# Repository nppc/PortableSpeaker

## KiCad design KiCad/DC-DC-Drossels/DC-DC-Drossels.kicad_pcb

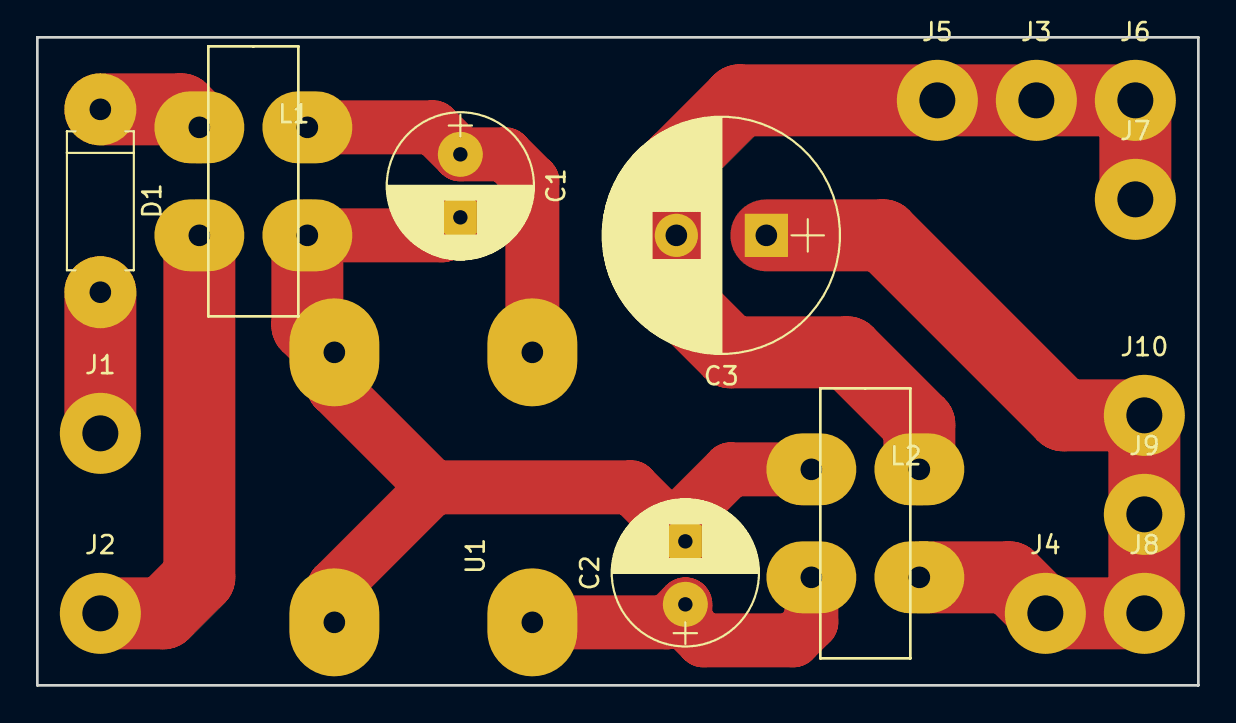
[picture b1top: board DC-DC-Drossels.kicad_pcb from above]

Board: 2 copper layers, 64.5 x 36.0 mm, 17 parts (0 on the bottom side), 8 nets.

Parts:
C1, C2: CP; CP_Radial_D8.0mm_P3.50mm
C3: CP; CP_Radial_D13.0mm_P5.00mm
D1: D_Schottky; D_DO-15_P10.16mm_Horizontal
J1, J2, J3, J4, J5, J6, J7, J8, J9, J10: Conn_01x01; SolderWirePad_single_2mmDrill
L1, L2: L_Core_Ferrite_Coupled; L_CommonMode_Wuerth_WE-CMB-XS
U1: MP1584ENBB; DIP-4_W7.62mm

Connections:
GND: C1.2, C2.2, L1.4, L2.1, U1.2, U1.3
unnamed: C1.1, L1.2, U1.1
unnamed: C2.1, L2.3, U1.4
unnamed: C3.1, J4.1, J8.1, J9.1, J10.1, L2.4
unnamed: C3.2, J3.1, J5.1, J6.1, J7.1, L2.2
unnamed: D1.1, L1.1
unnamed: D1.2, J1.1
unnamed: J2.1, L1.3

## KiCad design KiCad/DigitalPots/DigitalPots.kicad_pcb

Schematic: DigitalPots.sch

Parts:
C1: 2uf; C_0603
C2: 10n; C_0603
C3: 10uf; C_0603
C4: 100n; C_0603
J1: i2c; Conn_1x03_2.54mm
J2: 3; Conn_1x03_2.54mm
J3: 1; Conn_1x03_2.54mm
J4: 2; Conn_1x03_2.54mm
J5: 0; Conn_1x03_2.54mm
J6: Conn_01x02; Conn_1x02_2.54mm
J7: PWR; Conn_1x02_2.54mm
JP1: A0; SolderJumper-3_P1.3mm_Open_Pad1.0x1.5mm_NumberLabels
JP2: A1; SolderJumper-3_P1.3mm_Open_Pad1.0x1.5mm_NumberLabels
JP3: WP; SolderJumper-3_P1.3mm_Open_Pad1.0x1.5mm_NumberLabels
R1: 10k; R_0603
U1: LP2985-5.0; SOT-23-5
U2: IC20; TSSOP-20_4.4x6.5mm_Pitch0.65mm

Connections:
+9V: C1.1, J7.2, U1.1 (VIN), U1.3 (ON/~OFF~)
/A0: JP1.2, U2.4
/A1: JP2.2, U2.16
/RST: J6.1, R1.2, U2.15
/SCL: J1.3, U2.5
/SDA: J1.2, U2.6
/WP: J6.2, JP3.2, U2.14
GND: C1.2, C2.2, C3.2, C4.2, J1.1, J7.1, JP1.3, JP2.3, JP3.3, U1.2 (GND), U2.7
unnamed: C2.1, U1.4 (BP)
unnamed: J2.1, U2.3
unnamed: J2.2, U2.2
unnamed: J2.3, U2.1
unnamed: J3.1, U2.10
unnamed: J3.2, U2.9
unnamed: J3.3, U2.8
unnamed: J4.1, U2.20
unnamed: J4.2, U2.19
unnamed: J4.3, U2.18
unnamed: J5.1, U2.13
unnamed: J5.2, U2.12
unnamed: J5.3, U2.11
VCC: C3.1, C4.1, JP1.1, JP2.1, JP3.1, R1.1, U1.5 (VOUT), U2.17

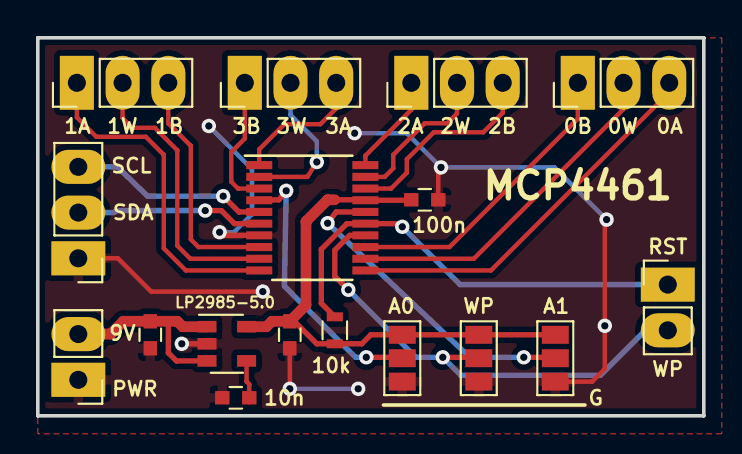
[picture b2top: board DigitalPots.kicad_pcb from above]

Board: 2 copper layers, 37.0 x 21.0 mm, 17 parts (0 on the bottom side), 22 nets.

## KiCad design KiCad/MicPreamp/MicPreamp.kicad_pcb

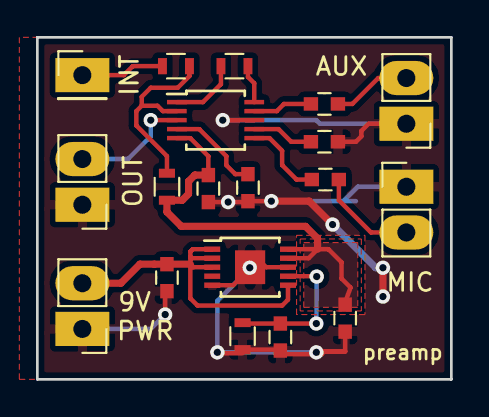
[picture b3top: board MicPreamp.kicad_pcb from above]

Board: 2 copper layers, 23.0 x 19.0 mm, 19 parts (0 on the bottom side), 15 nets.

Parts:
C1, C7: 100n; C_0603
C2, C8: 10uf; C_0603
C3: 0.47uf; C_0603
C4, C5, C6: 1uf; C_0603
J1: PWR; Conn_1x02_2.54mm
J2: INT; Conn_1x01_2.54mm
J3: OUT; Conn_1x02_2.54mm
J4: AUX; Conn_1x02_2.54mm
J5: MIC; Conn_1x02_2.54mm
R1: 100; R_0603
R2: 100K; R_0603
R3: 11K; R_0603
R4: 50K; R_0603
U1: MAX4062; TSSOP-10_3x3mm_Pitch0.5mm
U2: LT3042; MSOP-10-1EP_3x3mm_Pitch0.5mm

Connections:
+9V: C2.1, J1.2, U2.1, U2.2, U2.3, U2.6
/AUX_IN: C4.2, U1.9
/BIAS: C1.2, U1.4
/G1: R3.1, U1.10
/G2: R3.2, U1.1
/IN+: C6.2, U1.6
/IN-: C5.2, U1.7
/INT: R1.1, R2.1, U1.2
/OUT: J3.2, U1.3
GND: C1.1, C2.2, C3.2, C5.1, C7.2, C8.2, J1.1, J3.1, J4.1, J5.1, R4.1, U1.8, U2.5, U2.8, U2.11
unnamed: C3.1, R4.2, U2.7
unnamed: C4.1, J4.2
unnamed: C6.1, J5.2
unnamed: J2.1, R1.2
VCC: C7.1, C8.1, R2.2, U1.5, U2.9, U2.10

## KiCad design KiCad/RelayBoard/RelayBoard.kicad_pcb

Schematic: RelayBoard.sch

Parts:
C1, C2: 100uF; CP_Radial_D8.0mm_P3.50mm
J1: AMP1; Conn_Power
J2: AMP2; Conn_Power
J3: B_SENS; Conn_1x02_2.54mm
J4: CHG_OUT; Conn_Power
J5: BAT; Conn_Power
J6: CHG_IN; Conn_Power
J7: V27; Conn_Power
K1, K2: LY2NJ; Relay_LY2NJ
R1, R2: 220; R_Axial_DIN0414_L11.9mm_D4.5mm_P20.32mm_Horizontal

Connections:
GND: J6.1, J7.1, K1.1, K1.5, K2.1
unnamed: C1.2, K1.8, R1.1
unnamed: C2.2, K2.8, R2.1
unnamed: J1.1, J2.1, K1.6
unnamed: J1.2, J2.2, K1.3
unnamed 5: J5.1, K1.7, K2.5; also elsewhere on the board
unnamed 6: J5.2, K1.2, K2.4; also elsewhere on the board
unnamed: J4.1, K2.6
unnamed: J4.2, K2.3
VCC: C1.1, C2.1, J6.2, J7.2, K1.4, R1.2, R2.2

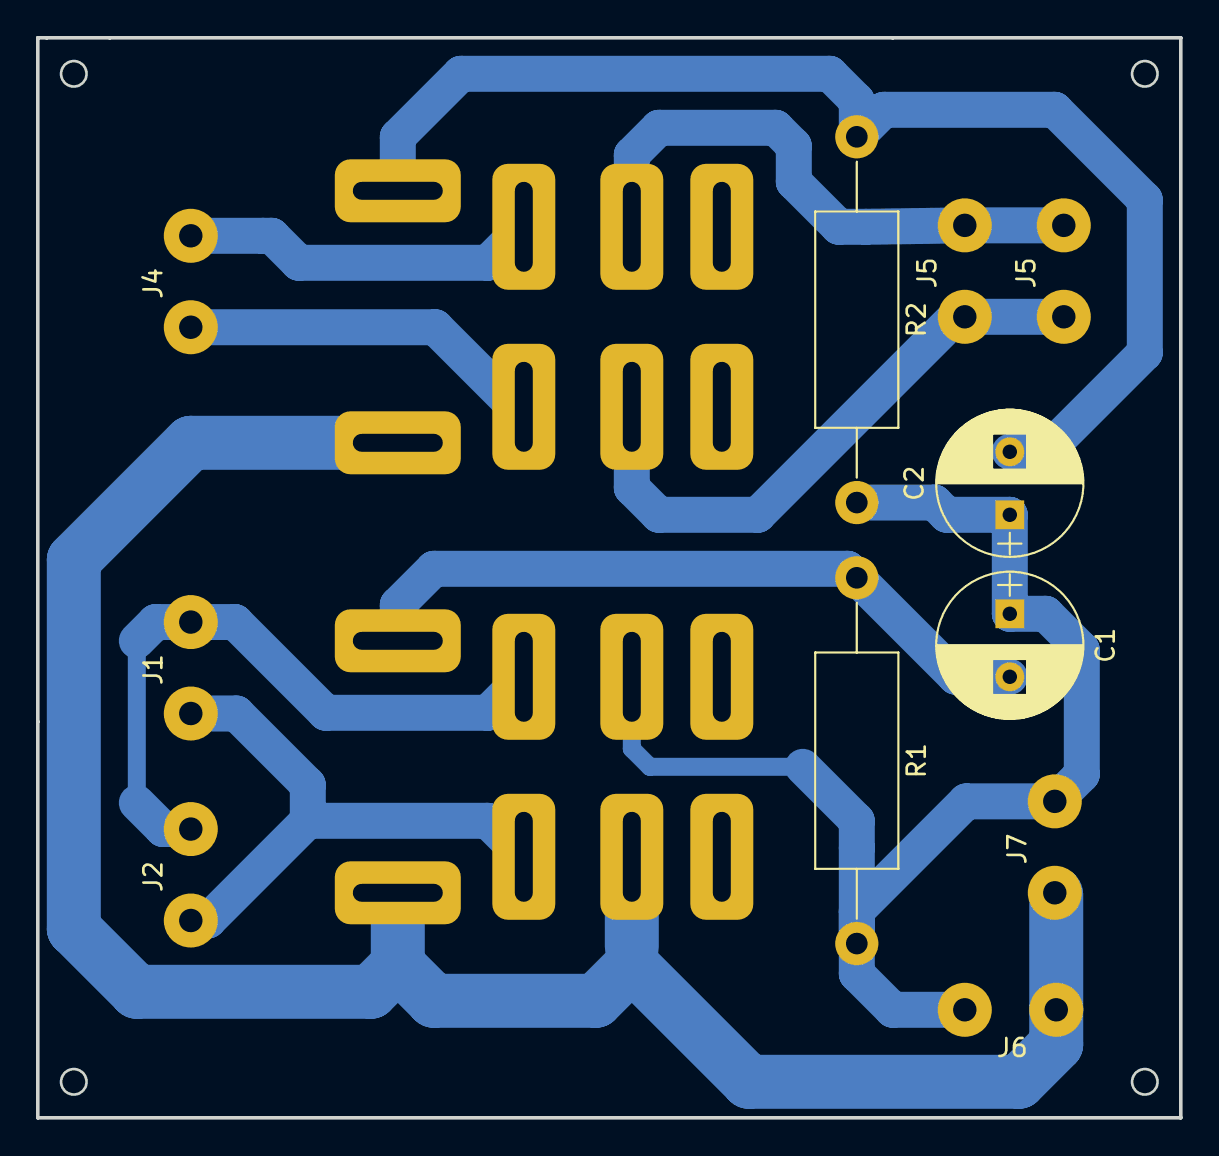
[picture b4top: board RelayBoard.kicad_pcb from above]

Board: 2 copper layers, 63.5 x 60.0 mm, 13 parts (0 on the bottom side), 10 nets.

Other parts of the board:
J5#2: BAT; Conn_Power

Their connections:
unnamed 5: J5#2.1; also elsewhere on the board
unnamed 6: J5#2.2; also elsewhere on the board

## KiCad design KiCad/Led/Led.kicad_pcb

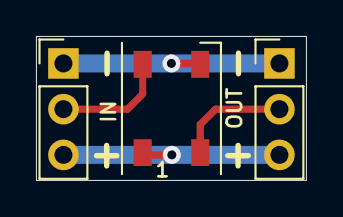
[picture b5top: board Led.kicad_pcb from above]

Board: 2 copper layers, 15.0 x 8.0 mm, 3 parts (0 on the bottom side), 4 nets.

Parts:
D1: WS2812B; LED_WS2812B_PLCC4_5.0x5.0mm_P3.2mm
J1: IN; PinHeader_1x03_P2.54mm_Vertical
J2: OUT; PinHeader_1x03_P2.54mm_Vertical

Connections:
unnamed: D1.1, J1.3, J2.3
unnamed: D1.2, J2.2
unnamed: D1.3, J1.1, J2.1
unnamed: D1.4, J1.2

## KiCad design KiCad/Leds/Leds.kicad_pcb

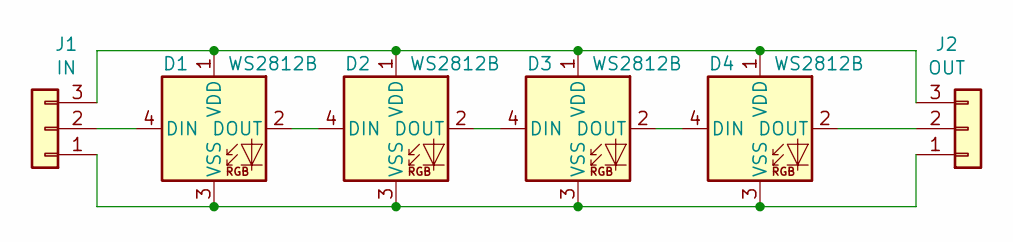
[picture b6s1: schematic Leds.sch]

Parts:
D1, D2, D3, D4: WS2812B; LED_WS2812B_PLCC4_5.0x5.0mm_P3.2mm
J1: IN; PinHeader_1x03_P2.54mm_Vertical
J2: OUT; PinHeader_1x03_P2.54mm_Vertical

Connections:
unnamed: D1.1 (VDD), D2.1 (VDD), D3.1 (VDD), D4.1 (VDD), J1.3, J2.3
unnamed: D1.2 (DOUT), D2.4 (DIN)
unnamed: D1.3 (VSS), D2.3 (VSS), D3.3 (VSS), D4.3 (VSS), J1.1, J2.1
unnamed: D1.4 (DIN), J1.2
unnamed: D2.2 (DOUT), D3.4 (DIN)
unnamed: D3.2 (DOUT), D4.4 (DIN)
unnamed: D4.2 (DOUT), J2.2

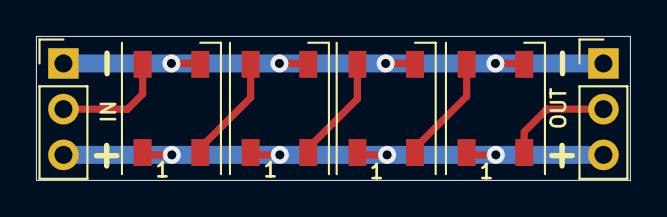
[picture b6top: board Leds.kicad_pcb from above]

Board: 2 copper layers, 33.0 x 8.0 mm, 6 parts (0 on the bottom side), 7 nets.

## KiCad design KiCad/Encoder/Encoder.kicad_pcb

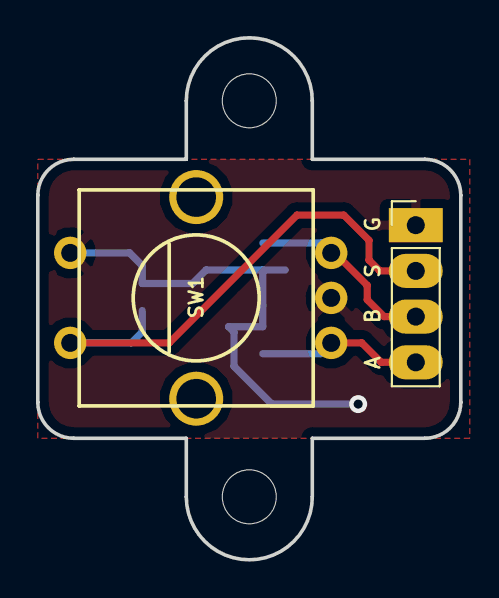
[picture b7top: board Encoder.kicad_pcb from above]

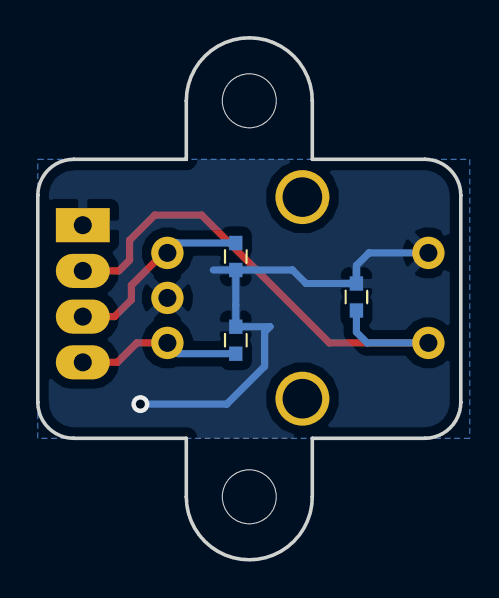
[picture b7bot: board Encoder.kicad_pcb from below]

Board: 2 copper layers, 23.5 x 29.0 mm, 5 parts (3 on the bottom side), 4 nets.

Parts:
C1, C2, C3: C_Small; C_0603
J1: Conn_01x04; Conn_1x04_2.54mm
SW1: Rotary_Encoder_Switch; ROTARY-ENCODER

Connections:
GND: C1.2, C2.2, C3.2, J1.1, SW1.2, SW1.5
unnamed: C1.1, J1.2, SW1.4
unnamed: C2.1, J1.4, SW1.1
unnamed: C3.1, J1.3, SW1.3

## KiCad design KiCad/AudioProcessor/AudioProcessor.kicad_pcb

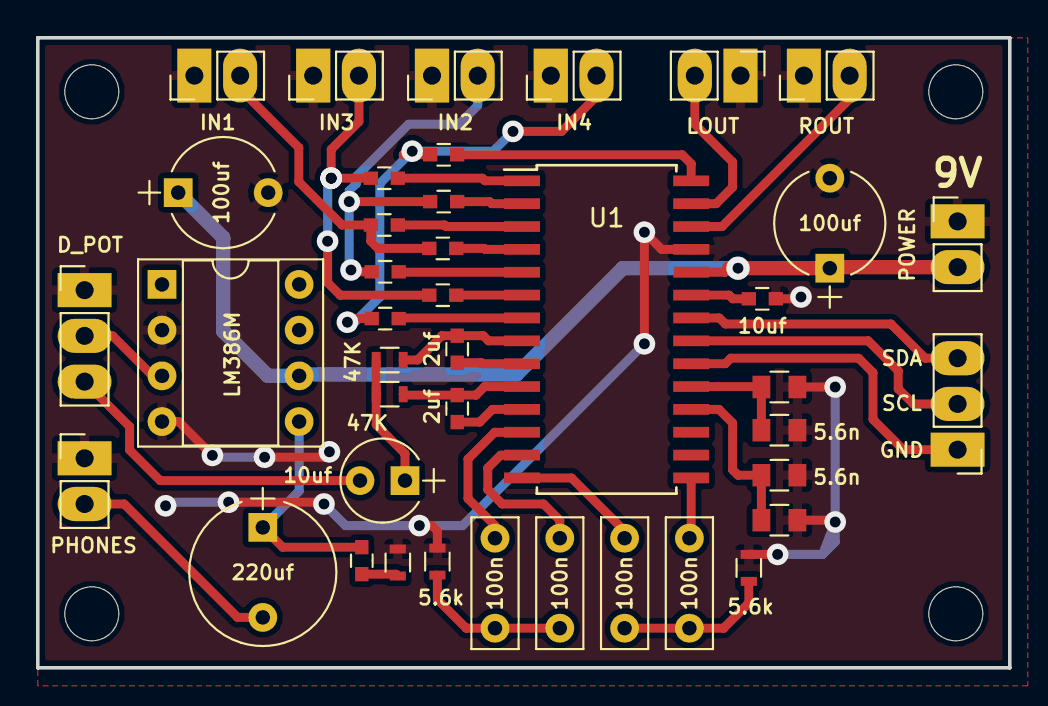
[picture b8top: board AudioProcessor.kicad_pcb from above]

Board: 2 copper layers, 54.0 x 35.0 mm, 41 parts (0 on the bottom side), 38 nets.

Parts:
C1: 220uf; CP_Radial_Tantal_D8.0mm_P5.00mm
C2: 50n; C_0603
C3, C22: 100uf; CP_Radial_Tantal_D6.0mm_P5.00mm
C4: 10uf; CP_Radial_Tantal_D4.5mm_P2.50mm
C5, C8, C9, C10: 100n; C_Rect_L7.2mm_W2.5mm_P5.00mm_FKS2_FKP2_MKS2_MKP2
C6, C7, C14, C15, C16, C17, C18, C19, C20, C21: 2uf; C_0603
C11, C23: 4.7n; C_0805
C12, C24: 1n; C_0805
C13: 10uf; C_0603
J1: IN4; Conn_1x02_2.54mm
J2: IN3; Conn_1x02_2.54mm
J3: IN2; Conn_1x02_2.54mm
J4: IN1; Conn_1x02_2.54mm
J5: PHONES; Conn_1x02_2.54mm
J6: I2C; Conn_1x03_2.54mm
J7: LOUT; Conn_1x02_2.54mm
J8: ROUT; Conn_1x02_2.54mm
J9: POWER; Conn_1x02_2.54mm
J10: D_POT; Conn_1x03_2.54mm
R1: 10; R_0603
R2, R3: 47K; R_0603
R9, R10: 5.6k; R_0603
U1: TDA7440; SOIC-28W_7.5x17.9mm_Pitch1.27mm
U2: LM386M; DIP-8_W7.62mm_Socket

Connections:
+9V: C3.1, C22.1, J9.2, U1.24, U2.6
/AUX: C4.2, J10.3
/GND: J6.1, U1.20
/IN1: C16.2, C19.2, J4.2
/IN2: C15.2, C20.2, J3.2
/IN3: C17.2, C18.2, J2.2
/IN4: C14.2, C21.2, J1.2
/LOUT: J7.2, U1.27
/ROUT: J8.2, U1.26
/SCL: J6.2, U1.21
/SDA: J6.3, U1.22
GNDA: C3.2, C11.1, C12.1, C13.1, C22.2, C23.1, C24.1, J1.1, J2.1, J3.1, J4.1, J5.1, J7.1, J8.1, J9.1, J10.1, R1.2, R9.2, R10.2, U1.25, U2.2, U2.4
unnamed: C1.1, C2.2, U2.5
unnamed: C1.2, J5.2
unnamed: C2.1, R1.1
unnamed: C4.1, R2.2, R3.2
unnamed: C5.1, C8.2, R9.1
unnamed: C5.2, U1.12
unnamed: C6.1, U1.9
unnamed: C6.2, R2.1, U1.8
unnamed: C7.1, U1.11
unnamed: C7.2, R3.1, U1.10
unnamed: C8.1, U1.13
unnamed: C9.2, U1.14
unnamed: C10.1, U1.15
unnamed: C9.1, C10.2, R10.1
unnamed: C11.2, C12.2, U1.19
unnamed: C13.2, U1.23
unnamed: C14.1, U1.28
unnamed: C15.1, U1.2
unnamed: C16.1, U1.4
unnamed: C17.1, U1.6
unnamed: C18.1, U1.1
unnamed: C19.1, U1.3
unnamed: C20.1, U1.5
unnamed: C21.1, U1.7
unnamed: C23.2, C24.2, U1.18
unnamed: J10.2, U2.3

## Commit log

2019-04-05 Add SCAD model
2019-04-07 Panel mostly done
2019-04-08 some parts replaced/added
2019-04-11 pcb cnc is ready
2019-04-12 firmware for audio processor
2019-04-12 some references changed
2019-04-12 test i2c
2019-04-12 testing sketch
2019-04-13 in progress
2019-04-14 Audio processor PCB is ready
2019-04-15 Mic preamp PCB done
2019-04-16 Adjust components according to availability
2019-04-16 Finished Arduino board
2019-04-16 Digital pots board ready
2019-04-17 Combined board
2019-04-17 PCB's finished and sent to JLPCB
2019-04-18 Combined board is changed as it was rejected by JLPCB
2019-04-18 Speakers diameter adjusted
2019-04-26 some CNC work done
2019-04-29 some adjustments to the scad according to real build
2019-05-01 some dxf/stl files added
2019-05-01 Charger Firmware
2019-05-02 added to charger firmware support for ws2812b
2019-05-02 test LED timing
2019-05-03 Another iteratoin with LED timing
2019-05-03 Some improvements over Danyy's code
2019-05-03 Add real oversampling and 16bit values for V and I
2019-05-03 Alfa version of Charger is ready. Not tested
2019-05-05 various work
2019-05-06 Some graphics added
2019-05-07 Separate code to different inos
2019-05-07 Fix Preamp board
2019-05-08 some audio functions created
2019-05-08 some audio functions added
2019-05-08 Volume control with encoder is tested and working
2019-05-09 Change volume from % to dB
2019-05-09 Prevent mutiple actions while encoder is pressed
2019-05-10 Show default screen after 30sec encoder idle
2019-05-10 Small issue with Treble is fixed
2019-05-10 Bezier calculation excel is added
2019-05-11 Digital POTs board test
2019-05-13 Add more routines for Digital Pot
2019-05-13 Digital Pots tested
2019-05-14 Add a real MUTE for Headphones
2019-05-14 Some filtering references added
2019-06-04 Store last project state
2019-06-05 3D models for lights
2019-06-07 Leds progress, some refs
2019-06-07 Leds scad model
2019-06-08 right side lights are ready
2019-06-08 remaining leds are ready
2019-06-19 Electronics holder and Encoder shaiba
2019-09-29 Input change
2020-03-15 FInished beta version of controller
2020-07-04 Mixer added
